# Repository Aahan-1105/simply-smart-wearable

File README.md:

# simply-wearable

## Overview
simply_wearable was created for the Half-Life program by hackclub for week 1: PCB Week.

I recently got a G-SHOCK and love it, but miss step counting from my old watch, so I decided to create a simple wearable with step tracking and a few buttons. I also decided to add a screen as a simple way to make it cooler without significant complexity. 

## Features
- BLE to phone
- Step counting
- oled screen with images and info
- 2 buttons for control
- Remote shutter for group photos
- Battery voltage monitoring
- 110maH battery with usb-c charging
- Built for under $30 USD

## Photos

Finished PCB Excluding Ground Fill

Finished Schematic

Renders of the PCB and CAD will be added as completed!

## BOM
|Purchase Status|Part              |Qty|Price (USD)|Total |Link                                                                                                                                                                                                                      |Shipping/Tax|Notes                           |
|---------------|------------------|---|-----------|------|--------------------------------------------------------------------------------------------------------------------------------------------------------------------------------------------------------------------------|------------|--------------------------------|
|               |301230 Battery    |1  |$10.05     |$10.05|https://www.aliexpress.com/item/1005005348368664.html?spm=a2g0o.cart.0.0.21be38dafBGUUp&mp=1&pdp_npi=6%40dis!CAD!CAD+15.74!CAD+8.22!!CAD+7.73!!!%402101c4b817914249992426203e0e42!12000032707728288!ct!CA!6705116064!!1!0!|            |Powers the wearable             |
|               |Passive components|1  |$4.92      |$4.92 |https://www.aliexpress.com/item/1005012364450156.html?spm=a2g0o.cart.0.0.d93b38da2l9jbS&mp=1&pdp_npi=6%40dis!USD!USD+2.83!USD+2.83!!USD+2.69!!!%402101c4b817914251483713919e0e42!12000058305516207!ct!CA!6705116064!!1!0! |            |Capacitor and buttons           |
|               |0.91" oled screen |1  |$3.58      |$3.58 |https://www.aliexpress.com/item/1005012327947468.html?spm=a2g0o.cart.0.0.21be38dafBGUUp&mp=1&pdp_npi=6%40dis!CAD!CAD+15.25!CAD+5.19!!CAD+5.14!!!%402101c4b817914249992426203e0e42!12000059297375602!ct!CA!6705116064!!1!0!|            |displaying info and cat gifs    |
|               |GY-BMI160         |1  |$1.62      |$1.62 |https://www.aliexpress.com/item/1005012327947468.html?spm=a2g0o.cart.0.0.21be38dafBGUUp&mp=1&pdp_npi=6%40dis!CAD!CAD+15.25!CAD+5.19!!CAD+5.14!!!%402101c4b817914249992426203e0e42!12000059297375602!ct!CA!6705116064!!1!0!|            |step counting!                  |
|               |PCB               |1  |$10.85     |$10.85|https://github.com/Aahan-1105/simply-wearable/blob/main/Images/JLCPCB_Cart.png                                                                                                                                            |            |Hold components and connect them|
|               |                  |   |           |      |                                                                                                                                                                                                                          |            |                                |
|               |                  |   |           |      |                                                                                                                                                                                                                          |            |                                |
|               |TOTAL (USD)       |   |$31.02     |$0.00 |                                                                                                                                                                                                                          |            |                                |
|               |TOTAL (CAD)       |   |$43.20     |$0.00 |                                                                                                                                                                                                                          |            |                                |

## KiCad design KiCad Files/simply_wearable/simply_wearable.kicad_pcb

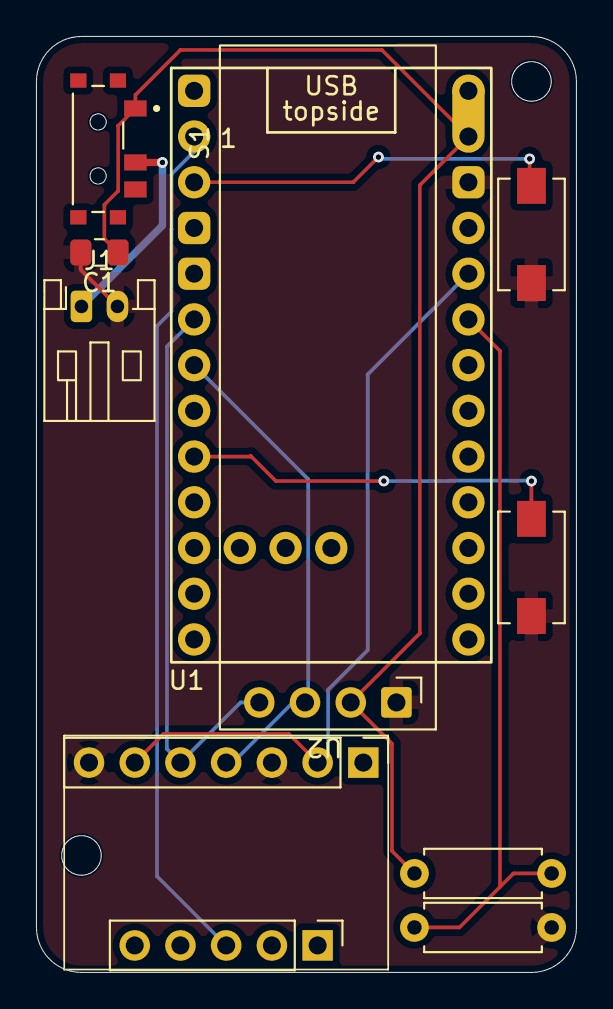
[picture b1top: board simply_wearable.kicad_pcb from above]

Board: 2 copper layers, 30.0 x 52.0 mm, 11 parts (0 on the bottom side), 10 nets.

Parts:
C1: C; C_0805_2012Metric_Pad1.18x1.45mm_HandSolder
J1: Conn_01x02_Socket; JST_PH_S2B-PH-K_1x02_P2.00mm_Horizontal
J3: Conn_01x07_Socket; PinHeader_1x07_P2.54mm_Vertical
J4: Conn_01x05_Socket; PinHeader_1x05_P2.54mm_Vertical
R3, R4: 10K; R_Axial_DIN0207_L6.3mm_D2.5mm_P7.62mm_Horizontal
S1: MSK12C02; SW_MSK12C02
SW1, SW2: SW_Push; SW_SPST_EVQPE1
U1: nice_nano; nice_nano_AH_USBup
U2: ER_OLEDM0.91_1x-I2C

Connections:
/3v3: J3.2, J3.6, U1.16 (3V3)
/BAT+: J1.1, S1.2
/GND: C1.2, J1.2, J3.3, J3.7, R4.2, SW1.2, SW2.2, U1.14 (GND), U2.1 (GND)
/INT1: J4.3 (Pin_3_3), U1.1 (P0.06)
/Primary: SW1.1, U1.2 (P0.08)
/SCL: J3.4, U1.6 (P0.20), U2.3 (SCL)
/SDA: J3.5, U1.5 (P0.17), U2.4 (SDA)
/Secondary: SW2.1, U1.8 (P0.24)
/VCC: C1.1, R3.1, S1.1, U1.13 (BAT+), U1.29 (BAT+), U2.2 (VCC)
unnamed: R3.2, R4.1, U1.17 (P0.31-LF)
